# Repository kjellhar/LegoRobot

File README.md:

# LegoRobot
Just various stuff to enable lego robots with non lego parts

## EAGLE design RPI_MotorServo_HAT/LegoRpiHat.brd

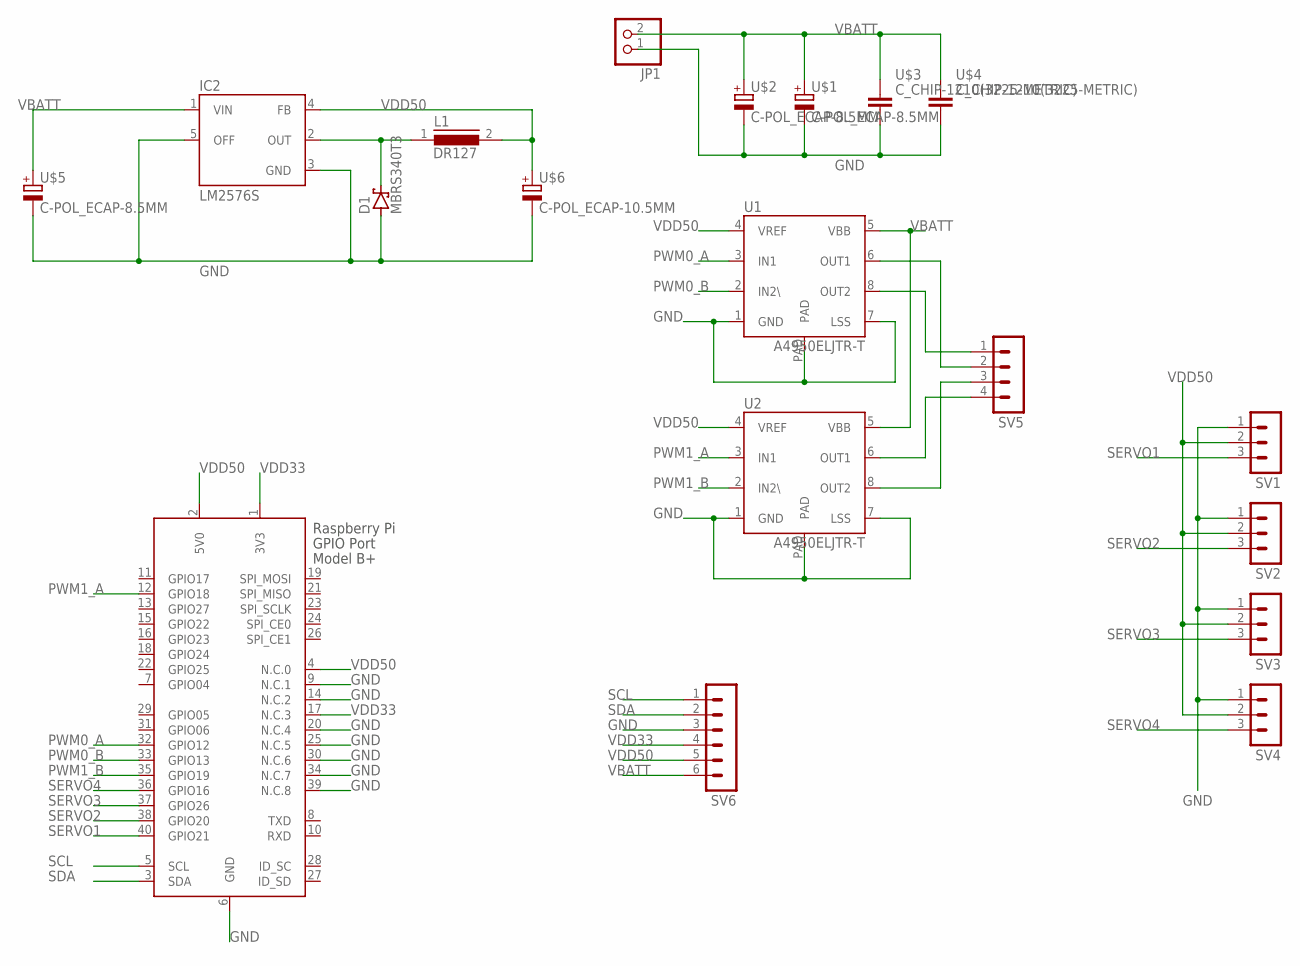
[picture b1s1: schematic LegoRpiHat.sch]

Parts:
D1: MBRS340T3; SMC
IC2: LM2576S; TO263-5
JP1: PINHD-1X2; 1X02
L1: DR127
SV1, SV2, SV3, SV4: MA03-1
SV5: MA04-1
SV6: MA06-1
U1, U2: A4950ELJTR-T; SOIC8TP
U$1, U$2, U$5: C-POL_ECAP-8.5MM; CAPAE830X1050N
U$3, U$4: C_CHIP-1210(3225-METRIC); CAPC3225X135
U$6: C-POL_ECAP-10.5MM; CAPAE1030X1050N
X1: RASPI_BOARD_B+_H; RASPI_BOARD_B+HAT

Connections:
GND: D1.A, IC2.3 (GND), IC2.5 (OFF), JP1.1, SV1.1, SV2.1, SV3.1, SV4.1, SV6.3, U1.1 (GND), U1.7 (LSS), U1.PAD, U2.1 (GND), U2.7 (LSS), U2.PAD, U$1.2 (-), U$2.2 (-), U$3.2, U$4.2, U$5.2 (-), U$6.2 (-), X1.6 (GND), X1.9 (N.C.1), X1.14 (N.C.2), X1.20 (N.C.4), X1.25 (N.C.5), X1.30 (N.C.6), X1.34 (N.C.7), X1.39 (N.C.8)
unnamed: D1.C, IC2.2 (OUT), L1.1
unnamed: SV5.2, U1.6 (OUT1)
unnamed: SV5.1, U1.8 (OUT2)
unnamed: SV5.4, U2.6 (OUT1)
unnamed: SV5.3, U2.8 (OUT2)
PWM0_A: U1.3 (IN1), X1.32 (GPIO12)
PWM0_B: U1.2 (IN2\), X1.33 (GPIO13)
PWM1_A: U2.3 (IN1), X1.12 (GPIO18)
PWM1_B: U2.2 (IN2\), X1.35 (GPIO19)
SCL: SV6.1, X1.5 (SCL)
SDA: SV6.2, X1.3 (SDA)
SERVO1: SV1.3, X1.40 (GPIO21)
SERVO2: SV2.3, X1.38 (GPIO20)
SERVO3: SV3.3, X1.37 (GPIO26)
SERVO4: SV4.3, X1.36 (GPIO16)
VBATT: IC2.1 (VIN), JP1.2, SV6.6, U1.5 (VBB), U2.5 (VBB), U$1.1 (+), U$2.1 (+), U$3.1, U$4.1, U$5.1 (+)
VDD33: SV6.4, X1.1 (3V3), X1.17 (N.C.3)
VDD50: IC2.4 (FB), L1.2, SV1.2, SV2.2, SV3.2, SV4.2, SV6.5, U1.4 (VREF), U2.4 (VREF), U$6.1 (+), X1.2 (5V0), X1.4 (N.C.0)

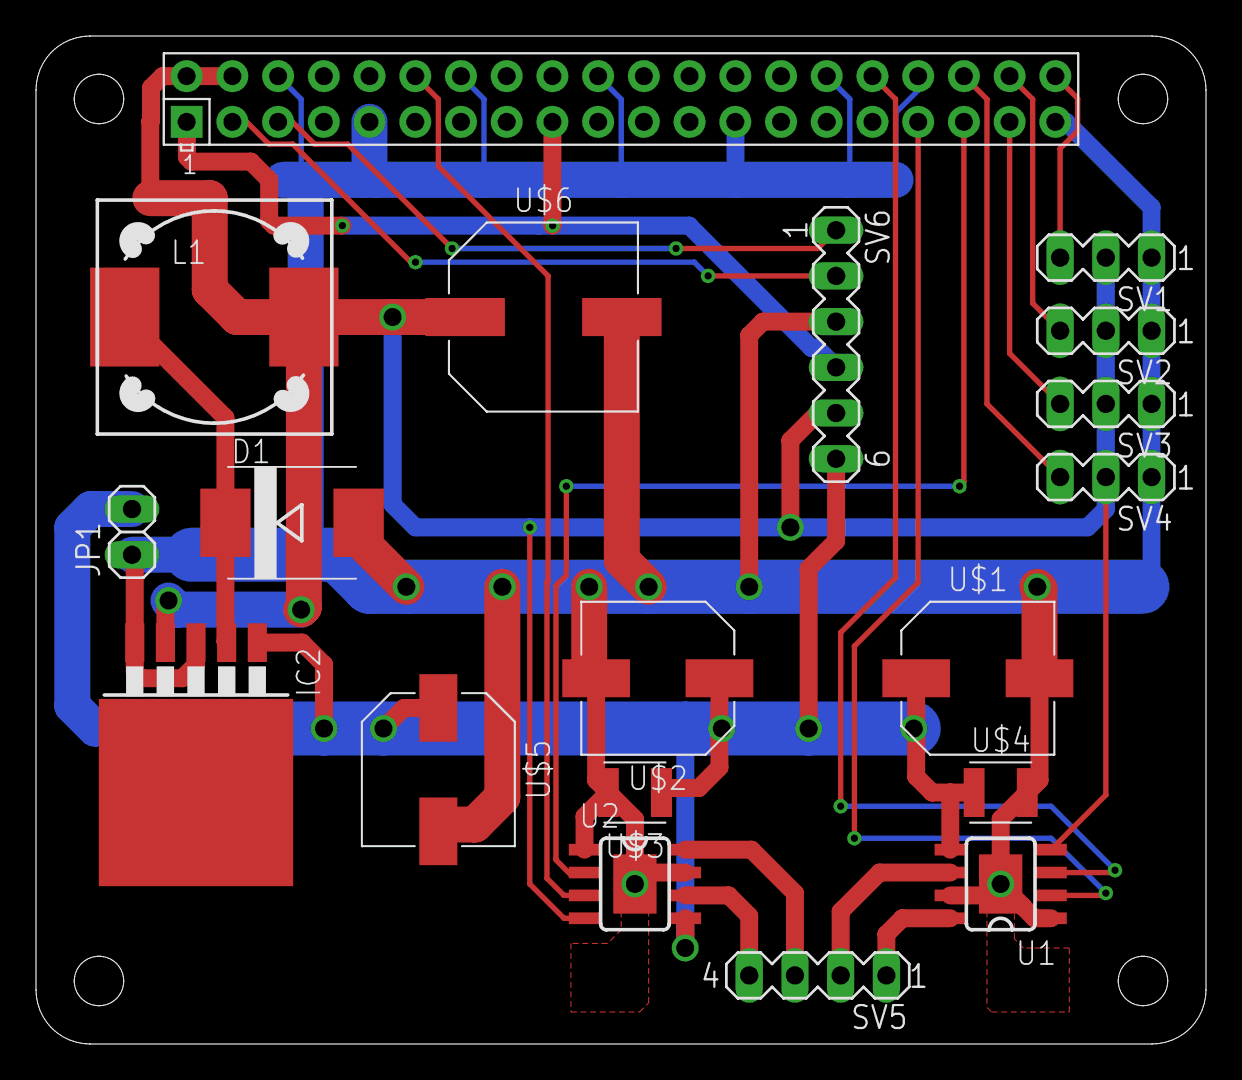
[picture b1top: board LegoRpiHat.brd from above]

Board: 2 copper layers, 65.0 x 56.0 mm, 19 parts (0 on the bottom side), 19 nets.

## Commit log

2020-02-12 Battery adapter for Bosch GBA12V batteries
    3D print this part to use your Bosch12V batteries in robot projects. This will fit the professional Bosch batteries, the ones that is used by the blue product line.
2020-02-12 RaspberryPi HAT for controlling 2 DC motors and 4 servos. There is also 8 general outputs and 8 general inputs. Not yet complete.
    This HAT is intended for a Lego robot project. For DC motors, bot Lego motors and other motors can be used, and for servos, ordinary RC servos using PWM control signals can be used. The servos must t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
2020-02-20 Started to make the connections. Still no passive components added
2020-02-20 mostly done with the schematics and the component placements. Only missing a couple of components on the 5V regulator
2020-02-21 More or less finishd. Removed al the GPIO due to space restrictions on a home made PCB
2020-03-05 Testing how to generate pcb mill output
